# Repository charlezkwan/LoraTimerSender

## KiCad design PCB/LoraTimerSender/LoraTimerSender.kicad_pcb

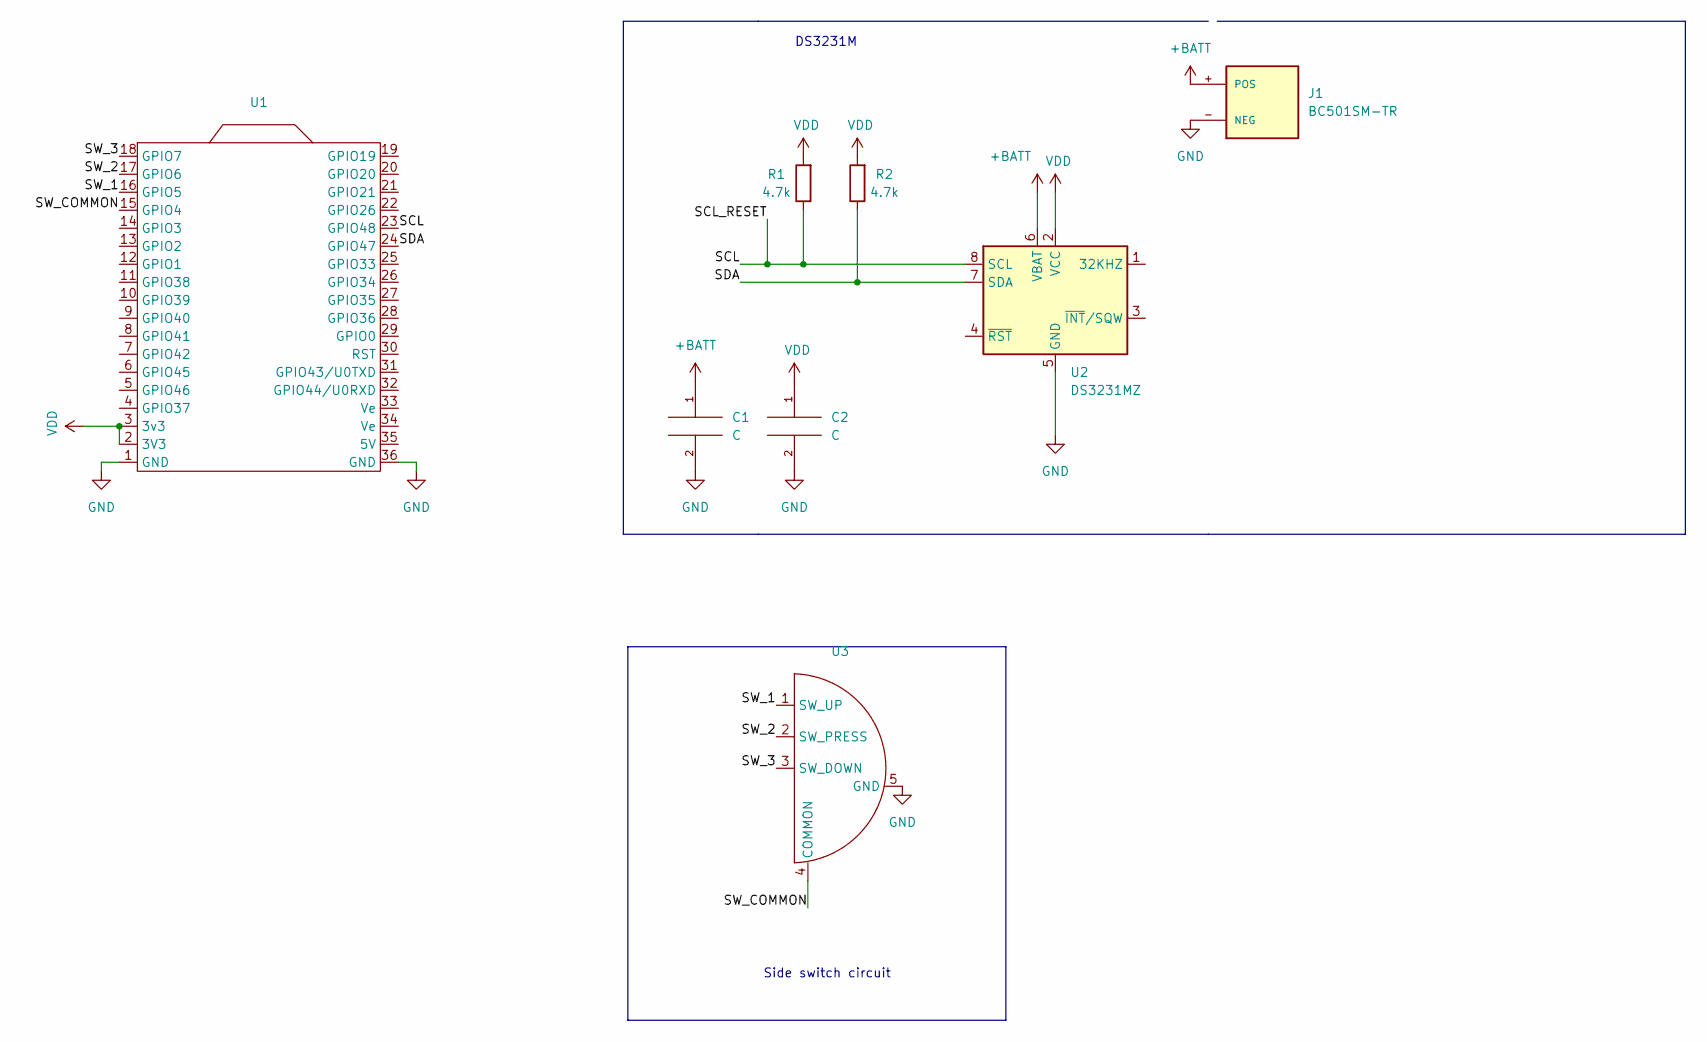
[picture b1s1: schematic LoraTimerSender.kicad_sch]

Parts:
C1: C; C_0805_2012Metric_Pad1.18x1.45mm_HandSolder
C2: C; C_0805_2012Metric
J1: BC501SM-TR; MPD_BC501SM-TR; PARTREV H
R1, R2: 4.7k; R_0805_2012Metric_Pad1.20x1.40mm_HandSolder
U1: MODULE_WIFI_KIT_32__V3_
U2: DS3231MZ; SOIC-8_3.9x4.9mm_P1.27mm
U3: NavigationSW

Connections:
+BATT: C1.1, J1.+ (POS), U2.6 (VBAT)
/SCL: R1.1, U1.23 (GPIO48), U2.8 (SCL)
/SDA: R2.1, U1.24 (GPIO47), U2.7 (SDA)
/SW_1: U1.16 (GPIO5), U3.1 (SW_UP)
/SW_2: U1.17 (GPIO6), U3.2 (SW_PRESS)
/SW_3: U1.18 (GPIO7), U3.3 (SW_DOWN)
/SW_COMMON: U1.15 (GPIO4), U3.4 (COMMON)
GND: C1.2, C2.2, J1.- (NEG), U1.1 (GND), U1.36 (GND), U2.5 (GND), U3.5 (GND)
VDD: C2.1, R1.2, R2.2, U1.2 (3V3), U1.3 (3v3), U2.2 (VCC)

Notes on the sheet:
DS3231M
Side switch circuit

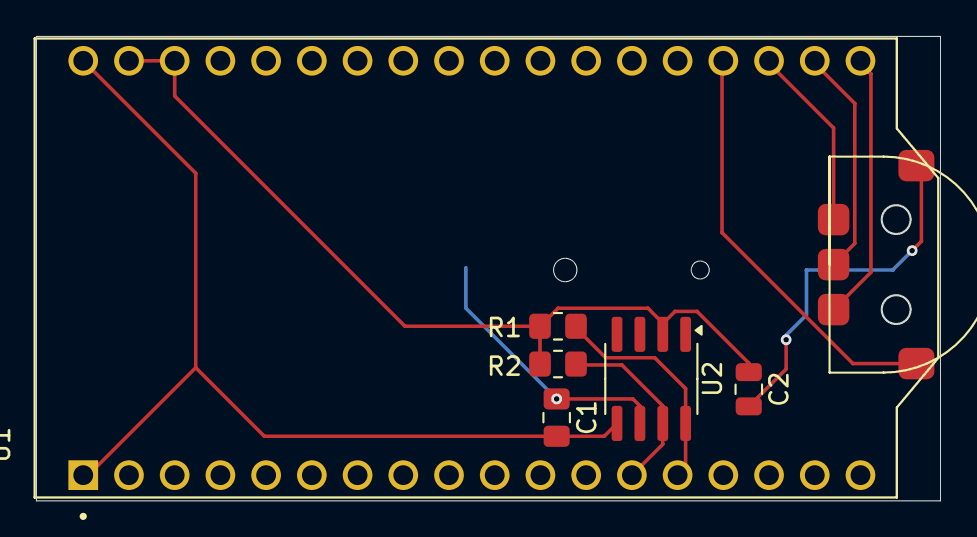
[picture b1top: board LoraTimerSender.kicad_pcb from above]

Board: 2 copper layers, 50.2 x 25.7 mm, 8 parts (1 on the bottom side), 9 nets.

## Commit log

2024-03-27 first
2024-07-26 added all working codes separately
